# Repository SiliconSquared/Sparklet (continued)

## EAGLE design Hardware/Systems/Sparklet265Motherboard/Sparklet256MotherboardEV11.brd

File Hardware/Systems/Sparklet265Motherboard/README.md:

# EagleCAD Hardware Design files for Sparklet 256X LED Motherboard

# Acknowledgments
The Booster/Charger module design in the Sparklet256XLEDMotherboard is based on the [Adafruit Powerboost 1000 Charger](https://www.adafruit.com/product/2465)

The amazing engineers at Adafruit created a perfectly optimized module to combine a LiPo charger and 5V booster at a current envelope within the limits of the Sparklet display. Thanks AdaFruit!

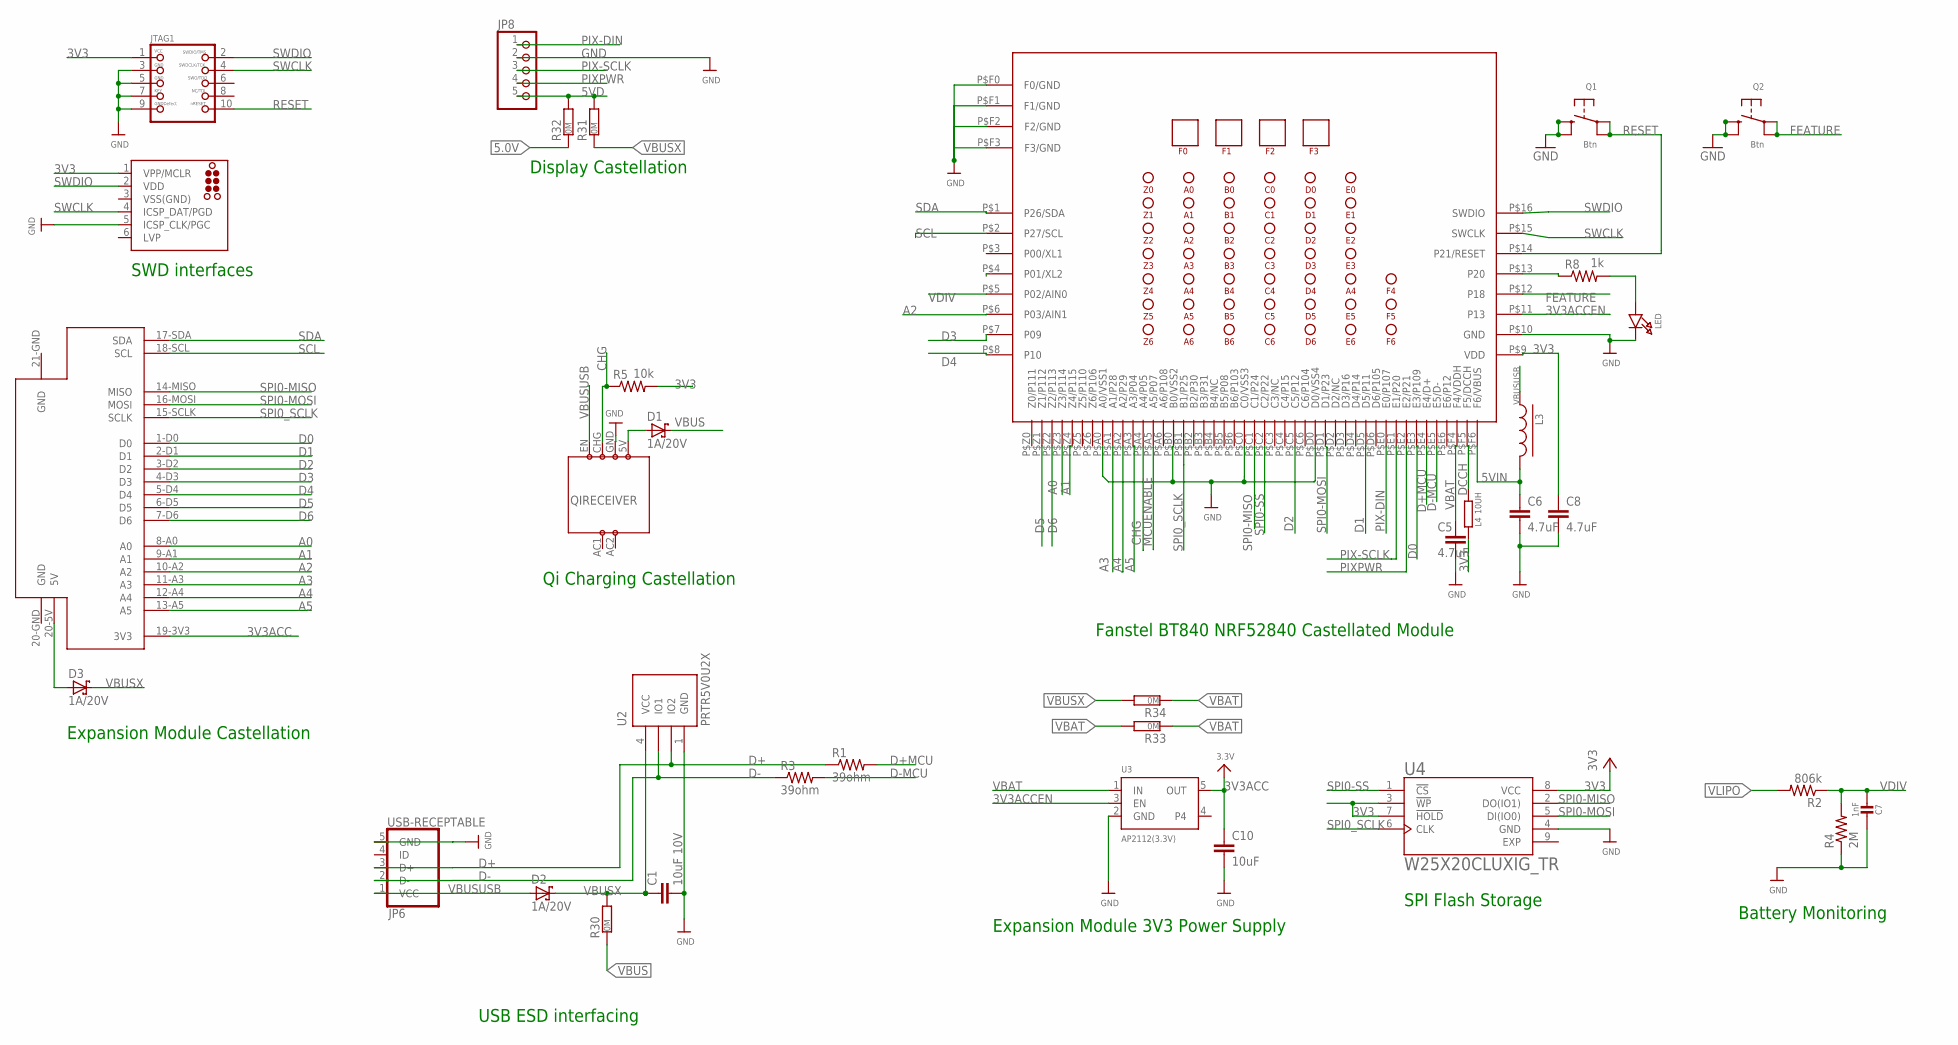
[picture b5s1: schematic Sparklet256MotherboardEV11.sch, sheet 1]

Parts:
C1: 10uF 10V; C0805
C5, C6, C8: 4.7uF; RESC0402_N
C7: 1nF; 0603-NO
C10: 10uF; RESC0402_N
D1, D2, D3: 1A/20V; SOD123
J2: TC2030-MCP-NL
JP6: USB-RECEPTABLE; FCI-10103594-0001LF
JP8: HEADER-1X5ROUND; 1X05_ROUND
JTAG1: JTAG-CORTEXM3; 2X05_1.27MM_SMT
L3: EXC3BP; L0603
L4: 10UH; R0603
LED: LED0805_NOOUTLINE; CHIPLED_0805_NOOUTLINE
Q1, Q2: Btn; BTN_KMR2_4.6X2.8
QIRECEIVER: CASTILQICHARGER
R1, R3: 39ohm; R0603
R2: 806k; R0603
R4: 2M; R0603
R5: 10k; R0603
R8: 1k; R0603
R30, R31, R32, R33, R34: 0M; RESC0805_N
U1: BT840
U2: PRTR5V0U2X; SOT-143B
U3: AP2112(3.3V); SOT23-5
U4: W25X20CLUXIG_TR; SON50P300X200X60-9N
U$2: EPX64MMEXPANSIONMODULE

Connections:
3V3: C8.1, J2.1 (VPP/MCLR), JTAG1.1, L4.1, R5.2, U1.P$9 (VDD), U4.3 (!WP), U4.7 (!HOLD), U4.8 (VCC)
3V3ACC: C10.1, U3.5 (OUT), U$2.19-3V3 (3V3)
3V3ACCEN: U1.P$11 (P13), U3.3 (EN)
5.0V: R32.1; also elsewhere on the board
5VD: JP8.5, R31.2, R32.2
5VIN: C6.1, L3.2, U1.P$F6 (F6/VBUS)
A0: U1.P$Z3 (Z3/P114), U$2.8-A0 (A0)
A1: U1.P$Z4 (Z4/P115), U$2.9-A1 (A1)
A2: U1.P$6 (P03/AIN1), U$2.10-A2 (A2)
A3: U1.P$A1 (A1/P28), U$2.11-A3 (A3)
A4: U1.P$A2 (A2/P29), U$2.12-A4 (A4)
A5: U1.P$A3 (A3/P04), U$2.13-A5 (A5)
AC1: QIRECEIVER.AC1
AC2: QIRECEIVER.AC2
CHG: QIRECEIVER.CHG, R5.1, U1.P$A4 (A4/P05)
D0: U1.P$E3 (E3/P109), U$2.1-D0 (D0)
D1: U1.P$D5 (D5/P11), U$2.2-D1 (D1)
D2: U1.P$C5 (C5/P12), U$2.3-D2 (D2)
D3: U1.P$7 (P09), U$2.4-D3 (D3)
D4: U1.P$8 (P10), U$2.5-D4 (D4)
D5: U1.P$Z1 (Z1/P112), U$2.6-D5 (D5)
D6: U1.P$Z2 (Z2/P113), U$2.7-D6 (D6)
D+: JP6.3 (D+), R1.1, U2.3 (IO2)
D+MCU: R1.2, U1.P$E4 (E4/D+)
D-: JP6.2 (D-), R3.1, U2.2 (IO1)
D-MCU: R3.2, U1.P$E5 (E5/D-)
DCCH: L4.2, U1.P$F5 (F5/DCCH)
EXPVBUS: D3.A, U$2.20-5V (5V)
FEATURE: Q2.A, Q2.A' (P1), U1.P$12 (P18)
GND: C1.2, C5.2, C6.2, C7.1, C8.2, C10.2, J2.5 (ICSP_CLK/PGC), JP6.5 (GND), JP8.2, JTAG1.3, JTAG1.5, JTAG1.7, JTAG1.9, LED.C, Q1.B (S), Q1.B' (S1), Q2.B (S), Q2.B' (S1), QIRECEIVER.GND, R4.1, U1.P$10 (GND), U1.P$A0 (A0/VSS1), U1.P$B0 (B0/VSS2), U1.P$C0 (C0/VSS3), U1.P$D0 (D0/VSS4), U1.P$F0 (F0/GND), U1.P$F1 (F1/GND), U1.P$F2 (F2/GND), U1.P$F3 (F3/GND), U2.1 (GND), U3.2 (GND), U4.4 (GND), U$2.20-GND (GND), U$2.21-GND (GND); also elsewhere on the board
MCUENABLE: U1.P$A5 (A5/P07); also elsewhere on the board
unnamed: D1.A, QIRECEIVER.5V
unnamed: R8.1, U1.P$13 (P20)
unnamed: LED.A, R8.2
PIX-DIN: JP8.1, U1.P$E0 (E0/P107)
PIX-SCLK: JP8.3, U1.P$E1 (E1/P20)
PIXPWR: JP8.4, U1.P$E2 (E2/P21)
RESET: JTAG1.10, Q1.A, Q1.A' (P1), U1.P$14 (P21/RESET)
SCL: U1.P$2 (P27/SCL), U$2.18-SCL (SCL)
SDA: U1.P$1 (P26/SDA), U$2.17-SDA (SDA)
SPI0-MISO: U1.P$C1 (C1/P24), U4.2 (DO(IO1)), U$2.14-MISO (MISO)
SPI0-MOSI: U1.P$D1 (D1/P23), U4.5 (DI(IO0)), U$2.16-MOSI (MOSI)
SPI0-SS: U1.P$C2 (C2/P22), U4.1 (!CS)
SPI0_SCLK: U1.P$B1 (B1/P25), U4.6 (CLK), U$2.15-SCLK (SCLK)
SWCLK: J2.4 (ICSP_DAT/PGD), JTAG1.4, U1.P$15 (SWCLK)
SWDIO: J2.2 (VDD), JTAG1.2, U1.P$16 (SWDIO)
VBAT: C5.1, R33.1, R33.2, R34.1, U1.P$F4 (F4/VDDH), U3.1 (IN); also elsewhere on the board
VBUS: R30.1; also elsewhere on the board
VBUSUSB: D2.A, JP6.1 (VCC), L3.1, QIRECEIVER.EN
VBUSX: C1.1, D1.C, D2.C, D3.C, R30.2, R31.1, R34.2, U2.4 (VCC)
VDIV: C7.2, R2.1, R4.2, U1.P$5 (P02/AIN0)
VLIPO: R2.2; also elsewhere on the board
VSS(GND): J2.3 (VSS(GND))

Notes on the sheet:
Battery Monitoring
Expansion Module Castellation
Display Castellation
SWD interfaces
USB ESD interfacing
Qi Charging Castellation
SPI Flash Storage
Expansion Module 3V3 Power Supply
Fanstel BT840 NRF52840 Castellated Module

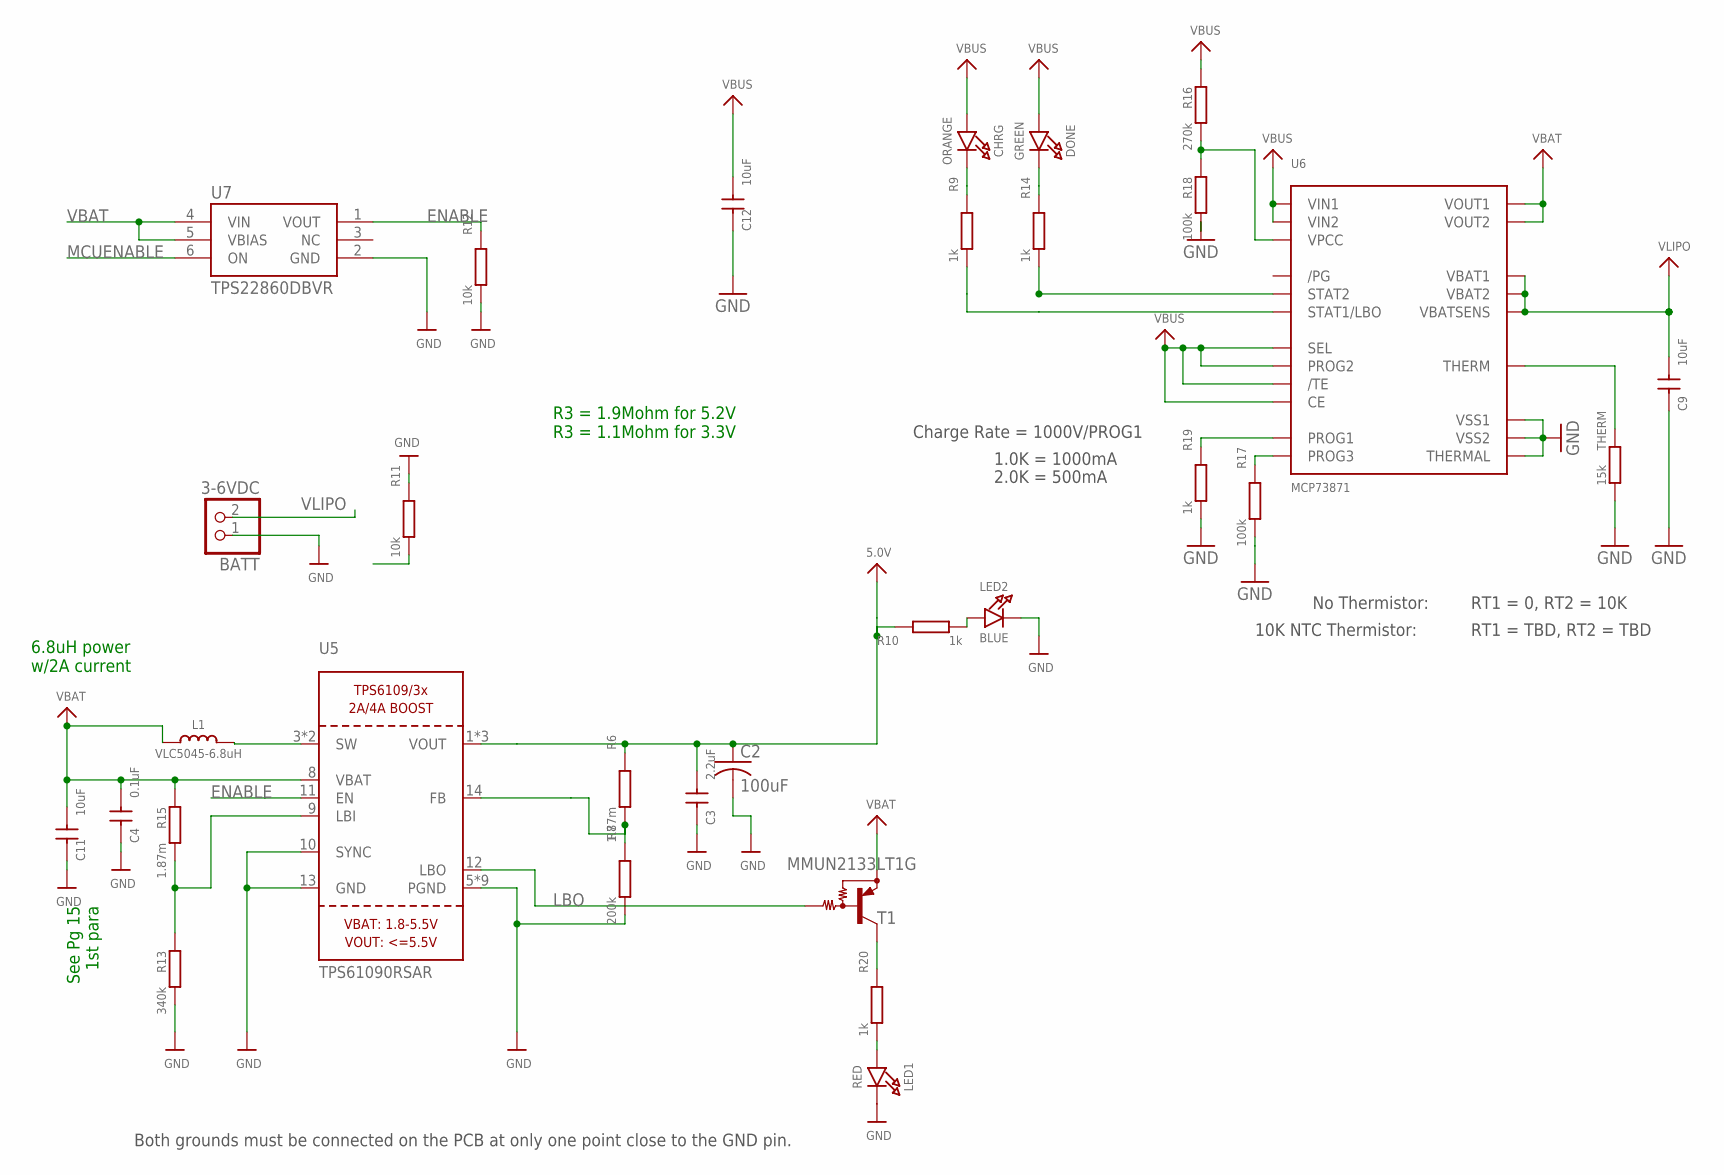
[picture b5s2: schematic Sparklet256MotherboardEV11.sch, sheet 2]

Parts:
BATT: 3-6VDC; JSTPH2
C2: 100uF; C1210
C3: 2.2uF; C-0402
C4: 0.1uF; C-0402
C9, C11, C12: 10uF; C-0402
CHRG: ORANGE; CHIPLED_0805_NOOUTLINE
DONE: GREEN; CHIPLED_0805_NOOUTLINE
L1: VLC5045-6.8uH; INDUCTOR_5X5MM_TDK_VLC5045
LED1: RED; CHIPLED_0805_NOOUTLINE
LED2: BLUE; CHIPLED_0805_NOOUTLINE
R6, R15: 1.87m; R0402
R7: 200k; R0402
R9, R10, R14, R19, R20: 1k; R0402
R11, R12: 10k; R0402
R13: 340k; R0402
R16: 270k; R0402
R17, R18: 100k; R0402
T1: MMUN2133LT1G; SC59-BEC
THERM: 15k; R0402
U5: TPS61090RSAR; PVQFN-16
U6: MCP73871; QFN20_4MM
U7: TPS22860DBVR; R-PDSO-G6

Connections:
5.0V: C2.1, C3.1, R6.1, R10.1, U5.1 (VOUT), U5.15 (VOUT), U5.16 (VOUT); also elsewhere on the board
ENABLE: R12.1, U5.11 (EN), U7.1 (VOUT)
GND: BATT.1, C2.2, C3.2, C4.2, C9.2, C11.2, C12.2, LED1.C, LED2.C, R7.2, R11.1, R12.2, R13.2, R17.2, R18.2, R19.2, THERM.2, U5.5 (PGND), U5.6 (PGND), U5.7 (PGND), U5.10 (SYNC), U5.13 (GND), U5.P$18 (PGND), U5.P$19 (PGND), U5.P$20 (PGND), U5.P$21 (PGND), U5.P$22 (PGND), U5.THERMAL (PGND), U6.P$10 (VSS1), U6.P$11 (VSS2), U6.P$21 (THERMAL), U7.2 (GND); also elsewhere on the board
LBO: T1.B, U5.12 (LBO)
MCUENABLE: R11.2, U7.6 (ON); also elsewhere on the board
unnamed: R13.1, R15.2, U5.9 (LBI)
unnamed: LED1.A, R20.2
unnamed: R6.2, R7.1, U5.14 (FB)
unnamed: R20.1, T1.C
unnamed: LED2.A, R10.2
unnamed: R16.2, R18.1, U6.P$2 (VPCC)
unnamed: R14.2, U6.P$7 (STAT2)
unnamed: R9.2, U6.P$8 (STAT1/LBO)
unnamed: THERM.1, U6.P$5 (THERM)
unnamed: DONE.C, R14.1
unnamed: CHRG.C, R9.1
unnamed: R19.1, U6.P$13 (PROG1)
unnamed: R17.1, U6.P$12 (PROG3)
unnamed: L1.P$2 (2), U5.3 (SW), U5.4 (SW)
VBAT: C4.1, C11.1, L1.P$1 (1), R15.1, T1.E, U5.8 (VBAT), U6.P$1 (VOUT1), U6.P$20 (VOUT2), U7.4 (VIN), U7.5 (VBIAS); also elsewhere on the board
VBUS: C12.1, CHRG.A, DONE.A, R16.1, U6.P$3 (SEL), U6.P$4 (PROG2), U6.P$9 (/TE), U6.P$17 (CE), U6.P$18 (VIN1), U6.P$19 (VIN2); also elsewhere on the board
VLIPO: BATT.2, C9.1, U6.P$14 (VBAT1), U6.P$15 (VBAT2), U6.P$16 (VBATSENS); also elsewhere on the board

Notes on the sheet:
Both grounds must be connected on the PCB at only one point close to the GND pin.
See Pg 15 1st para
6.8uH power w/2A current
R3 = 1.9Mohm for 5.2V R3 = 1.1Mohm for 3.3V
Charge Rate = 1000V/PROG1
1.0K = 1000mA
2.0K = 500mA
No Thermistor:
10K NTC Thermistor:
RT1 = 0, RT2 = 10K
RT1 = TBD, RT2 = TBD

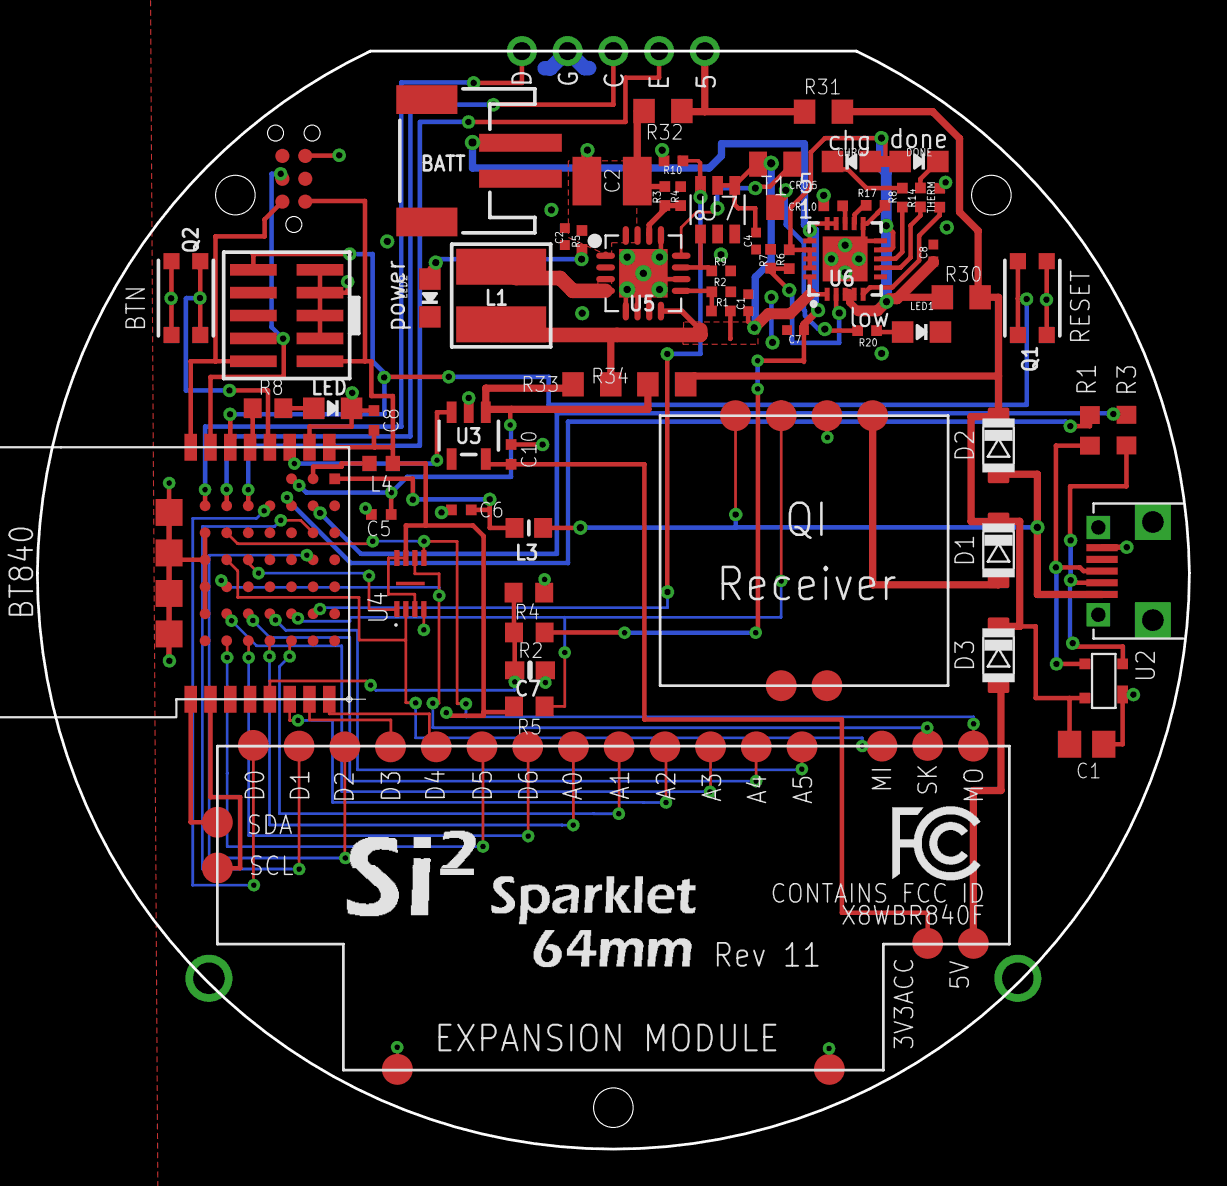
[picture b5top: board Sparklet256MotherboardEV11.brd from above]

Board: 2 copper layers, 64.0 x 61.0 mm, 66 parts (0 on the bottom side), 66 nets.

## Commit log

2020-08-29 Open source upload
2020-08-29 Upload
2020-09-02 Upload accessories
2020-09-02 Asset
2020-09-02 Update parts list.txt
    Corrected the part number for the required 8 inch 18 lb zip tie that fits in the Zip Tie version of the Action Camera mount.
2020-09-02 Added Expansion Modules
2020-09-03 Added FW versioning
2020-09-03 Latest FW images
2020-11-11 1.45 FIRMWARE
2020-11-13 Bug fix
